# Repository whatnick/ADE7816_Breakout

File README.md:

# Breakout Board for ADE7816 6-Channel Energy Monitor ASIC

For those wanting to monitor lots of individual channels in a single-phase household the
[ADE7816](https://www.analog.com/en/products/ade7816.html)
is an ideal solution. It allows differential current sensors for 3 channels and single ended current
sensors for 3 more channels. The MCU interface is over SPI or I2C bus, and Arduino driver will
be developed along with this breakout board.

## Supporting Software

There is work in progress on supporting this board in [Arduino](https://github.com/whatnick/ADE7816_Arduino) and [Micropython](https://github.com/whatnick/ade7816_micropython).

## Getting the hardware

The hardware can be obtained as PCB, PCB + Parts Kit or Fully assembled.

- [Tindie Fully assembled](https://www.tindie.com/stores/whatnick/)
- [Aisler partkit](https://aisler.net/whatnick/playground/ade7816-breakout)
- [OSHPark PCB](https://oshpark.com/shared_projects/oovHySXk)
- [PCBWay PCB](https://www.pcbway.com/project/shareproject/Breakout_Board_for_ADE7816_6_Channel_Energy_Monitor_ASIC.html)

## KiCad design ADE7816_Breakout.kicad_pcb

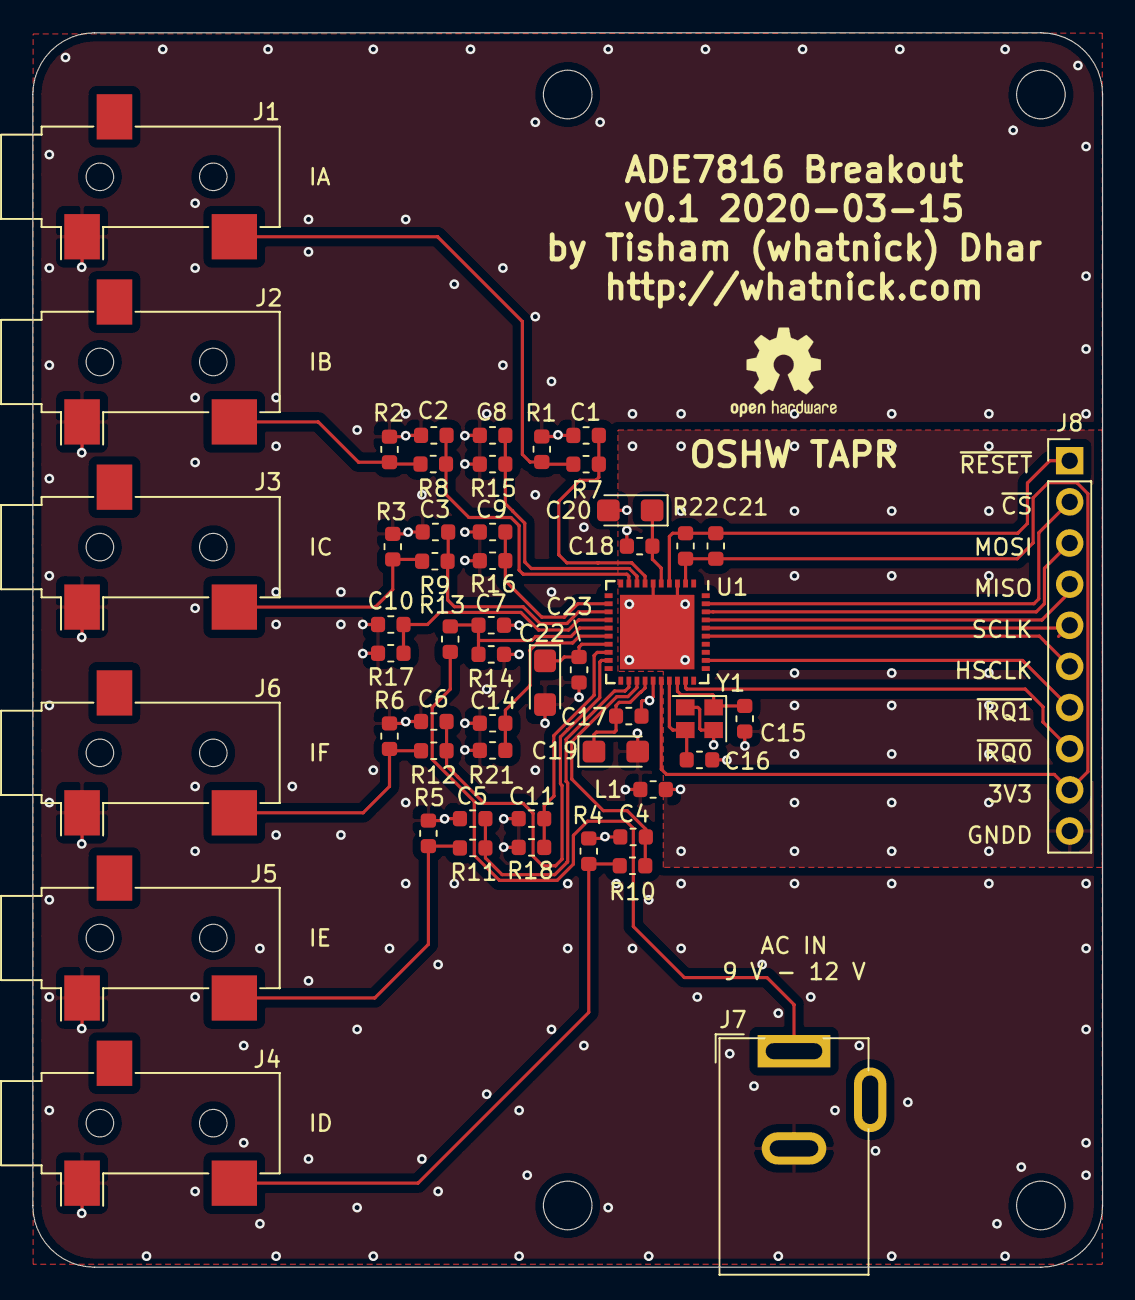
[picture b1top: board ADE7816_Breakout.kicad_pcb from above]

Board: 2 copper layers, 66.0 x 76.2 mm, 57 parts (0 on the bottom side), 35 nets.

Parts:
C1, C2, C3, C4, C5, C6, C7, C8, C9, C10, C11, C14: 22n; C_0603_1608Metric
C15, C16: 20p; C_0603_1608Metric
C17, C18, C23: 220n; C_0603_1608Metric
C19, C20, C22: 4.7u; CP_EIA-3216-18_Kemet-A
C21: 1u; C_0603_1608Metric
H1, H2, H3, H4: MountingHole; MountingHole_3mm
J1, J2, J3, J4, J5, J6: AudioJack3; Jack_3.5mm_CUI_SJ-3523-SMT_Horizontal
J7: Barrel_Jack_Switch; Barrel_Jack_CUI_PJ-002A
J8: Conn_01x10; PinHeader_1x10_P2.54mm_Vertical
L1: Ferrite; L_0603_1608Metric
LOGO1: Logo_Open_Hardware_Small; OSHW-Logo2_7.3x6mm_SilkScreen
R1, R2, R3, R4, R5, R6: 4.7R; R_0603_1608Metric
R7, R8, R9, R10, R11, R12, R14, R15, R16, R17, R18, R21: 1k; R_0603_1608Metric
R13: 100k; R_0603_1608Metric
R22: 10k; R_0603_1608Metric
U1: ADE7816ACPZ; QFN-40-1EP_6x6mm_Pitch0.5mm
Y1: 16.384MHz; Crystal_SMD_2520-4Pin_2.5x2.0mm

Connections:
+3V3: C21.1, J8.9, R22.1, U1.2, U1.26
/analog_inputs/IA: J1.2, R1.2, R7.2
/analog_inputs/IB: J2.2, R2.2, R8.2
/analog_inputs/IC: J3.2, R3.2, R9.2
/analog_inputs/ID: J4.2, R4.2, R10.2
/analog_inputs/IE: J5.2, R5.2, R11.2
/analog_inputs/IF: J6.2, R6.2, R12.2
/meter_module/AVDD: C17.1, C19.1, U1.24
/meter_module/CLKIN: C16.2, U1.27, Y1.3
/meter_module/CLKOUT: C15.2, U1.28, Y1.1
/meter_module/DVDD: C18.1, C20.1, U1.5
/meter_module/HSCLK: J8.6, U1.35
/meter_module/MISO: J8.4, U1.37
/meter_module/MOSI: J8.3, U1.38
/meter_module/SCLK: J8.5, U1.36
/meter_module/~CS: J8.2, U1.39
/meter_module/~IRQ0: J8.8, U1.29
/meter_module/~IRQ1: J8.7, U1.32
/meter_module/~RESET: C21.2, J8.1, R22.2, U1.4
GNDA: C1.2, C2.2, C3.2, C4.2, C5.2, C6.2, C7.2, C8.2, C9.2, C10.2, C11.2, C14.2, C17.2, C19.2, C22.2, C23.2, J1.1, J2.1, J3.1, J4.1, J5.1, J6.1, J7.2, L1.1, R1.1, R2.1, R3.1, R4.1, R5.1, R6.1, R14.2, R15.1, R16.1, R17.1, R18.1, R21.2, U1.25
GNDD: C15.1, C16.1, C18.2, C20.2, J8.10, L1.2, U1.3, U1.6, U1.41, Y1.2, Y1.4
IAN: C8.1, R15.2, U1.8
IAP: C1.1, R7.1, U1.7
IBN: C9.1, R16.2, U1.12
IBP: C2.1, R8.1, U1.9
ICN: C10.1, R17.2, U1.14
ICP: C3.1, R9.1, U1.13
IDP: C4.1, R10.1, U1.23
IEP: C5.1, R11.1, U1.22
IFP: C6.1, R12.1, U1.19
IN: C11.1, R18.2, U1.18
unnamed: C22.1, C23.1, U1.17
unnamed: J7.1, R13.2
VN: C14.1, R21.1, U1.16
VP: C7.1, R13.1, R14.1, U1.15

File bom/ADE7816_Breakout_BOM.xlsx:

References | manf# | Value | Footprint | Quantity
C1, C2, C3, C4, C5, C6, C7, C8, C9, C10, C11, C14 | GCE188R71H223KA01D | 22n | C_0603_1608Metric | 12
C15, C16 | GCM1885C2A200JA16D | 20p | C_0603_1608Metric | 2
C17, C18, C23 | GCM188R71E224KA55D | 220n | C_0603_1608Metric | 3
C21 | GRT188C8YA105KE13D | 1u | C_0603_1608Metric | 1
C19, C20, C22 | TAJA475K016UNJ | 4.7u | CP_EIA-3216-18_Kemet-A | 3
R1, R2, R3, R4, R5, R6 | CRL0603-FW-4R70ELF | 4.7R | R_0603_1608Metric | 6
R13 | RT0603FRE10100KL | 100k | R_0603_1608Metric_Pad1.05x0.95mm_HandSolder | 1
R7, R8, R9, R10, R11, R12, R14, R15, R16, R17, R18, R21 | RT0603FRE101KL | 1k | R_0603_1608Metric | 12
R22 | RT0603FRE1310KL | 10k | R_0603_1608Metric | 1
L1 | BLM18KG300TN1D | Ferrite | L_0603_1608Metric | 1
U1 | ADE7816ACPZ | ADE7816ACPZ | QFN-40-1EP_5x5mm_P0.4mm_EP3.6x3.6mm_ThermalVias | 1
Y1 | ABM10-16.384MHZ-D30-T3 | 16.384MHz | Crystal_SMD_2520-4Pin_2.5x2.0mm | 1
J7 | PJ-002A | Barrel_Jack_Switch | BarrelJack_Horizontal | 1
J1, J2, J3, J4, J5, J6 | SJ-3523-SMT-TR | AudioJack3 | Jack_3.5mm_CUI_SJ-3523-SMT_Horizontal | 6

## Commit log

2020-02-17 Initial import
2020-02-17 Add readme
2020-02-18 Add doc snippets and extra sheets
2020-02-21 Start adding analog inputs and filters
2020-02-21 Add crystal load caps
2020-02-22 Add more parts and placements
2020-02-23 Initial round of schematic parts
2020-02-23 Add part numbers and begin placement
2020-02-24 make ridiculously thin traces for route attempt
2020-02-27 Some routing
2020-02-28 Violate DRC and get some routing done
2020-02-29 Get some sort of 100% routing with DRC broken
2020-02-29 Output Gerbers
2020-02-29 Add stitching vias
2020-02-29 Regen gerbers
2020-02-29 Update BOM
2020-03-11 Modified the library symbols used for the stereo jack and DC jack. Made stereo jack footprint reference local copy in folder lib/misc.pretty to avoid compatibility issues between different versions o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
2020-03-12 - Updated U1 to use QFN40 6x6mm 0.5 pitch on both schematic and PCB and updated the layout to accomidate this. - moved all footprint files to the modules directory - created modified footprint for th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
2020-03-15 Add silk screen details
2020-03-15 Label nets for currents
2020-03-15 Add more silk screen
2020-03-16 Add WIP render
2020-03-16 New IBOM
2020-03-16 New Gerbers
2020-03-16 Add placement file
2020-04-09 Added assembled board photos
2020-04-15 Update Readme with manufacturer / sale links
